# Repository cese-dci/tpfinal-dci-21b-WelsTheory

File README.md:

## Trabajo práctico final de la asignatura DCI ##
Este repositorio contiene el trabajo práctico final para la asignatura de Diseño de Circuitos Impresos de la carrera de posgrado de FIUBA.

* Autor: William's Ernesto Limonchi Sandoval
* Tí­tulo corto del trabajo: Módulo para STM32
* Descripción:  Módulo detector de caídas para Núcleo STM32

## Licencia de este trabajo ##
Este producto es de código abierto !

El hardware es liberado bajo [Creative Commons ShareAlike 4.0 International](https://creativecommons.org/licenses/by-sa/4.0/).

Puede utilizar, reutilizar y modificar el proyecto como mejor le parezca. Mantenga la atribución a Wels Theory

Saludos

## Estructura del TP FINAL ##

Se propone y se pide utilizar la siguiente estructura.

* doc: Toda la información sobre el circuito, principalmente de autorí­a o procesamiento propio. Por ejemplo:
  * Notas de ingeniería propias.
  * Notas de aplicación propias.
  * Estudios previos, estado del arte, resumen de las investigaciones.
  * Notas con cálculos.
  * Dibujos adicionales.
  * Fotos de los prototipos.
  * Presupuestos, cotizaciones.
* info: Toda la información recolectada, principalmente de terceros, como por ejemplo:
  * Hojas de datos.
  * Notas de aplicación.
  * Info de productos comerciales.
  * Info en internet.
* pcb: Archivos de diseño esquemático y pcb.

Dependiendo la magnitud del proyecto, tendremos más o menos información en estos directorios. 
Revisar los README.md en cada directorio para conocer las pautas de cada uno para este TP.

NOTA: El alumno puede y debe borrar de este archivo todo lo que considere necesario, por ejemplo las aclaraciones del docente y esta misma nota.

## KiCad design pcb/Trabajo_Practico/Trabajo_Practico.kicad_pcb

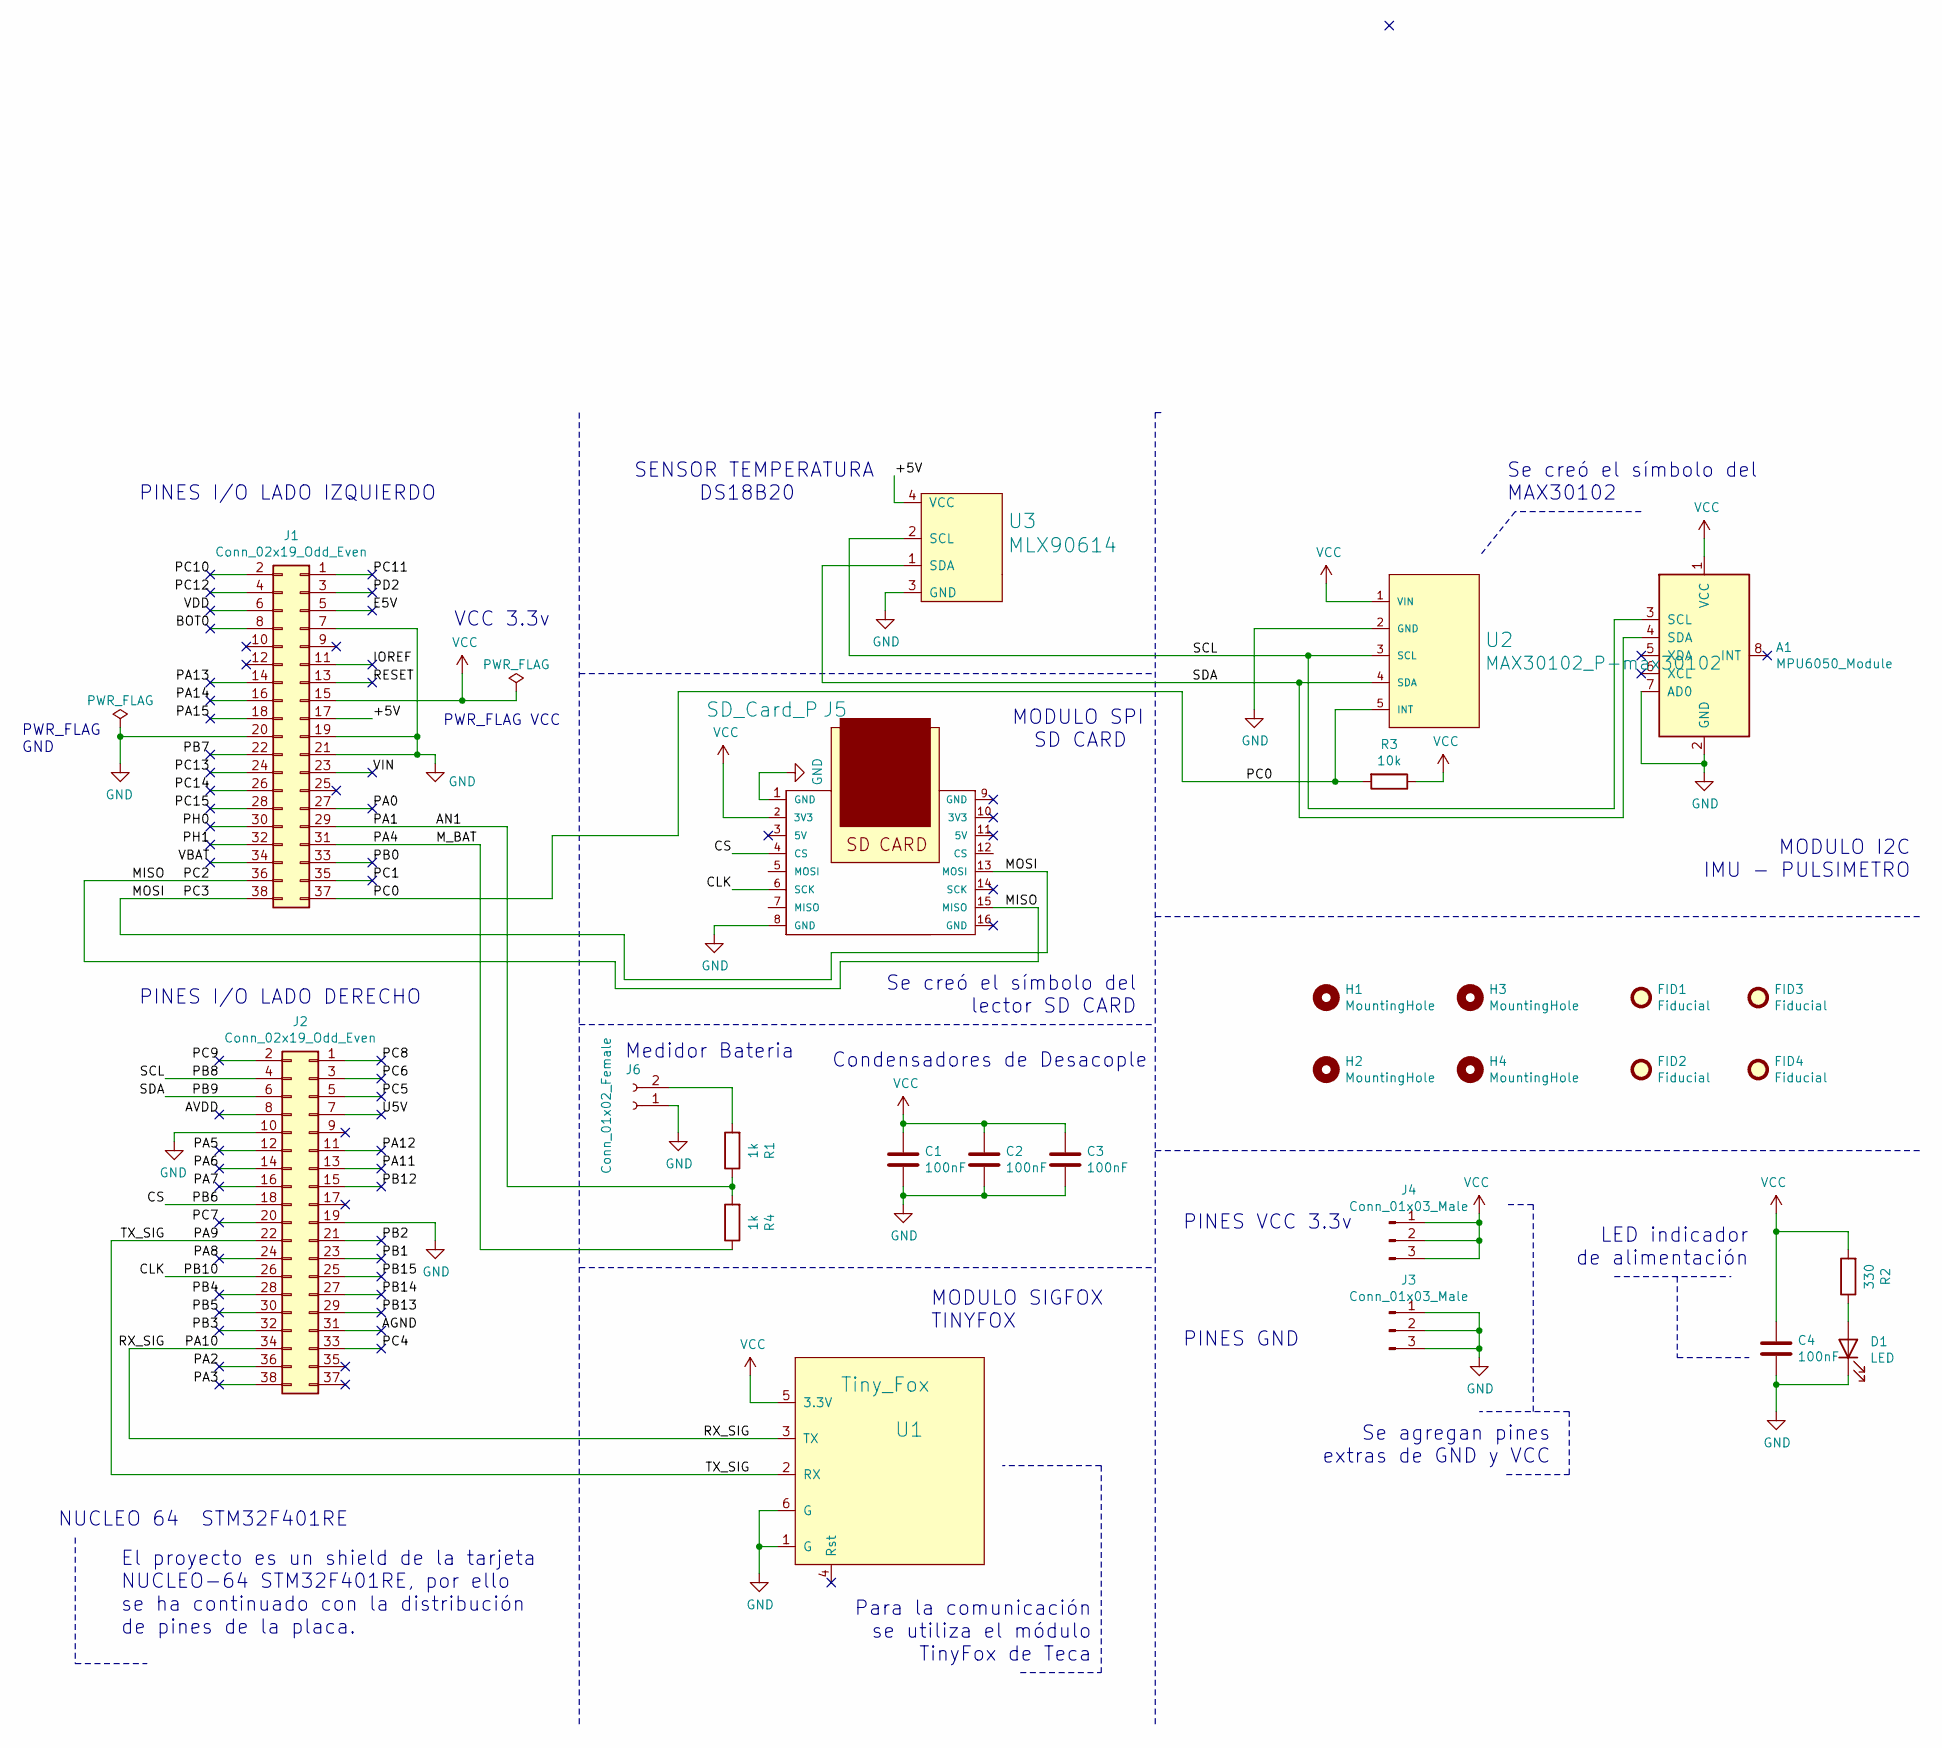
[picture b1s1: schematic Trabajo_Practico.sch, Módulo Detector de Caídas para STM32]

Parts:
A1: MPU6050_Module
C1, C2, C3, C4: 100nF; C_0805_2012Metric
D1: LED; LED_0805_2012Metric_Pad1.15x1.40mm_HandSolder
FID1, FID2, FID3, FID4: Fiducial; Fiducial_0.5mm_Mask1mm
H1, H2, H3, H4: MountingHole; MountingHole_2.2mm_M2_Pad_Via
J1, J2: Conn_02x19_Odd_Even; PinSocket_2x19_P2.54mm_Vertical
J3, J4: Conn_01x03_Male; PinHeader_1x03_P2.54mm_Vertical
J5: SD_Card_P; SD_CARD_P
J6: Conn_01x02_Female; PinSocket_1x02_P2.54mm_Vertical
R1, R4: 1k; R_0805_2012Metric
R2: 330; R_0805_2012Metric
R3: 10k; R_0805_2012Metric
U1: Tiny_Fox; TinyFox
U2: MAX30102_P-max30102; MAX30102_P
U3: MLX90614

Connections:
/+5V: J1.17, U3.4 (VCC)
/AGND: J2.31
/AN1: J1.29, R1.1, R4.2
/AVDD: J2.8
/BOT0: J1.8
/CLK: J2.26, J5.6 (SCK)
/CS: J2.18, J5.4 (CS)
/E5V: J1.5
/IOREF: J1.11
/MISO: J1.36, J5.15 (MISO)
/MOSI: J1.38, J5.13 (MOSI)
/M_BAT: J1.31, R4.1
/PA0: J1.27
/PA2: J2.36
/PA3: J2.38
/PA5: J2.12
/PA6: J2.14
/PA7: J2.16
/PA8: J2.24
/PA9: J2.22, U1.2 (RX)
/PA10: J2.34, U1.3 (TX)
/PA11: J2.13
/PA12: J2.11
/PA13: J1.14
/PA14: J1.16
/PA15: J1.18
/PB0: J1.33
/PB1: J2.23
/PB2: J2.21
/PB3: J2.32
/PB4: J2.28
/PB5: J2.30
/PB7: J1.22
/PB8: A1.3 (SCL), J2.4, U2.3 (SCL), U3.2 (SCL)
/PB9: A1.4 (SDA), J2.6, U2.4 (SDA), U3.1 (SDA)
/PB12: J2.15
/PB13: J2.29
/PB14: J2.27
/PB15: J2.25
/PC0: J1.37, R3.2, U2.5 (INT)
/PC1: J1.35
/PC4: J2.33
/PC5: J2.5
/PC6: J2.3
/PC7: J2.20
/PC8: J2.1
/PC9: J2.2
/PC10: J1.2
/PC11: J1.1
/PC12: J1.4
/PC13: J1.24
/PC14: J1.26
/PC15: J1.28
/PD2: J1.3
/PH0: J1.30
/PH1: J1.32
/RESET: J1.13
/U5V: J2.7
/VBAT: J1.34
/VDD: J1.6
/VIN: J1.23
GND: A1.2 (GND), A1.7 (AD0), C1.2, C2.2, C3.2, C4.2, D1.1 (K), J1.7, J1.19, J1.20, J1.21, J2.10, J2.19, J3.1, J3.2, J3.3, J5.1 (GND), J5.8 (GND), J6.1, U1.1 (G), U1.6 (G), U2.2 (GND), U3.3 (GND)
unnamed: D1.2 (A), R2.1
unnamed: J6.2, R1.2
VCC: A1.1 (VCC), C1.1, C2.1, C3.1, C4.1, J1.15, J4.1, J4.2, J4.3, J5.2 (3V3), R2.2, R3.1, U1.5 (3.3V), U2.1 (VIN)

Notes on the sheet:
MODULO SIGFOX TINYFOX
SENSOR TEMPERATURA DS18B20
MODULO SPI SD CARD
NUCLEO 64 STM32F401RE
Condensadores de Desacople
PINES I/O LADO IZQUIERDO
PINES I/O LADO DERECHO
PINES VCC 3.3v
Para la comunicación se utiliza el módulo TinyFox de Teca
MODULO I2C IMU - PULSIMETRO
PINES GND
El proyecto es un shield de la tarjeta NUCLEO-64 STM32F401RE, por ello se ha continuado con la distribución de pines de la placa.
Se agregan pines extras de GND y VCC
Se creó el símbolo del lector SD CARD
Se creó el símbolo del MAX30102
PWR_FLAG VCC
PWR_FLAG GND
VCC 3.3v
LED indicador de alimentación
Medidor Bateria

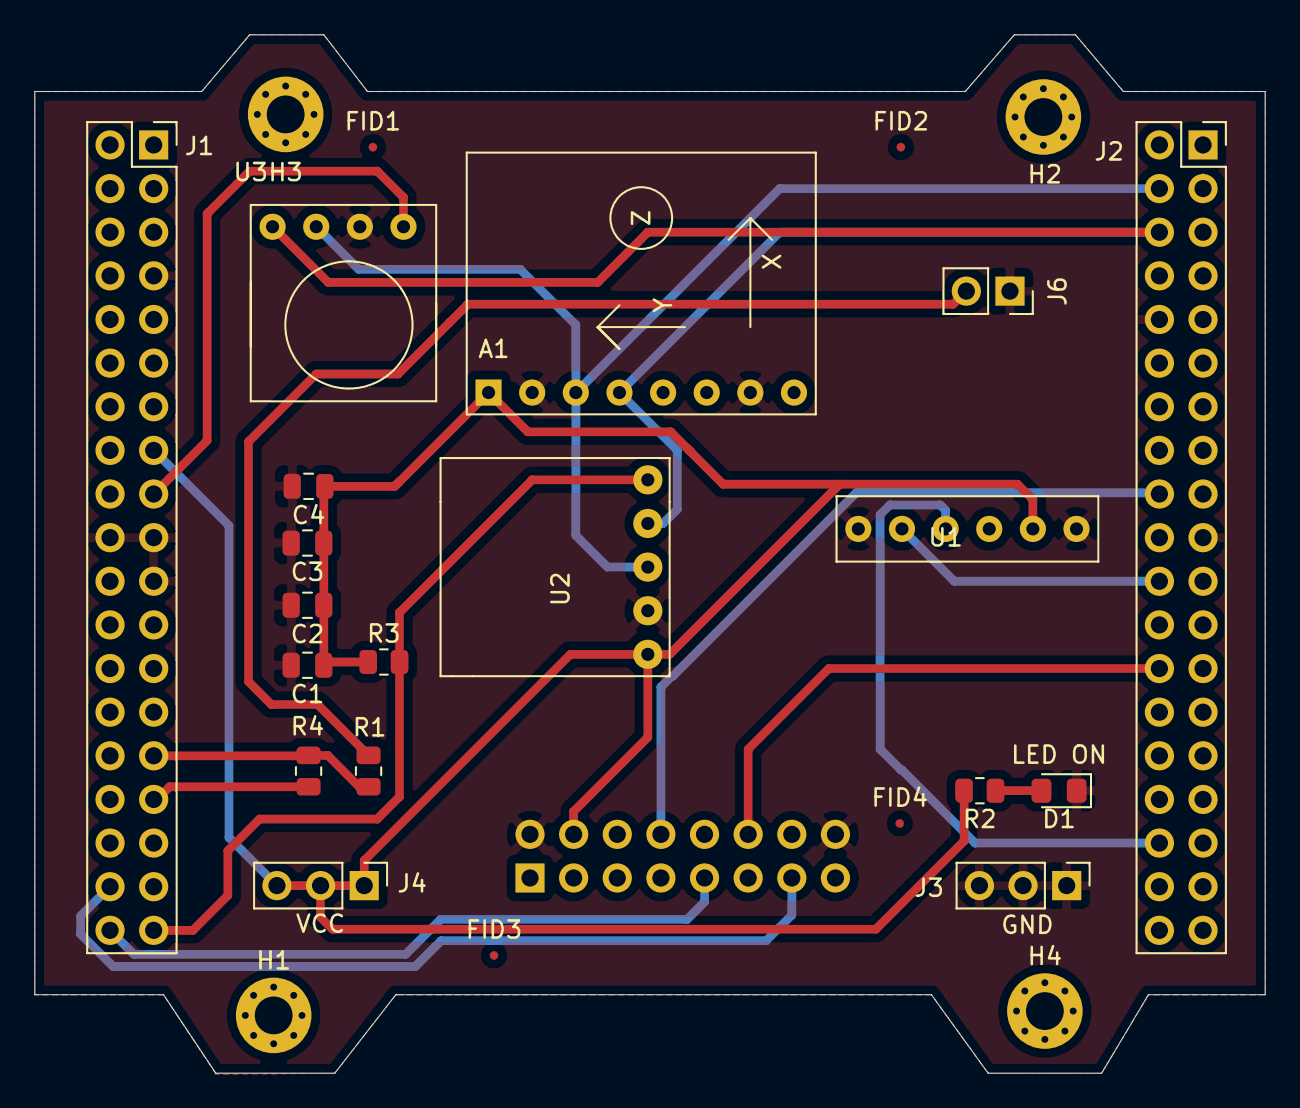
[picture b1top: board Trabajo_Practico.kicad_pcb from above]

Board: 2 copper layers, 71.6 x 60.5 mm, 27 parts (1 on the bottom side), 16 nets.

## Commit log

2021-08-09 Se terminó el esquemático y agregaron simbolos y huellas diseñadas
2021-08-09 Se agrega el Power Flag
2021-08-10 Se ordena los componentes en el pcb
2021-08-12 Se realizaron las correcciones
2021-08-16 Presentacion final del proyecto
2021-08-16 Realizaron correcciones en Readme y agregó documentación
2021-10-17 Agrego sensor MLX90614

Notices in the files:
pcb/Trabajo_Practico/Trabajo_Practico.kicad_pcb:
Licencia GNU GPL
